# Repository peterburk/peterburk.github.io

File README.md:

# About Me

##Current Location
Auckland, New Zealand

##Email
peterburk at gmail dot com

##Qualifications
- MEng Electronic Systems Engineering, Lancaster University: First-class Honours
- International Baccalaureate

##Awards
- Lancaster Award (extra-curricular)
- IET Scholarship

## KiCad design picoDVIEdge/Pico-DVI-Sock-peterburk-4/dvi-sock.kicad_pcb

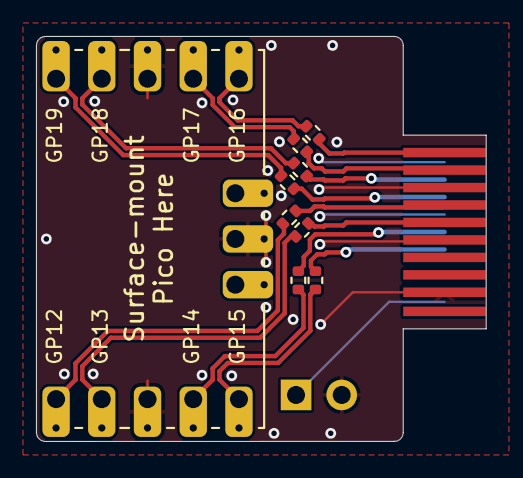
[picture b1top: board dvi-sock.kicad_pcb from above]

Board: 2 copper layers, 25.0 x 22.5 mm, 13 parts (0 on the bottom side), 18 nets.

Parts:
J1, J2: Conn_01x05; castellated_2.54mm_smd_x5
J3: Conn_01x03; castellated_2.54mm_smd_x3
J5: 2.54mm_2p_nofit; PinHeader_1x02_P2.54mm_Vertical_nosilk
R1, R2, R3, R4, R5, R6, R7, R8: 270; R_0402_1005Metric
U1: hdmiFemale

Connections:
+5V: J5.1, U1.18 +5V PWR
/CK+: R7.2, U1.10 TMDS CLK+
/CK-: R8.2, U1.12 TMDS CLK-
/D0+: R5.2, U1.7 TMDS Channel 0+
/D0-: R6.2, U1.9 TMDS Channel 0-
/D1+: R3.2, U1.4 TMDS Channel 1+
/D1-: R4.2, U1.6 TMDS Channel 1 -
/D2+: R1.2, U1.1 TMDS Channel 2+
/D2-: R2.2, U1.3 TMDS Channel 2-
/PICO_CK+: J1.4, R7.1
/PICO_CK-: J1.5, R8.1
/PICO_D0+: J1.1, R5.1
/PICO_D0-: J1.2, R6.1
/PICO_D1+: J2.4, R3.1
/PICO_D1-: J2.5, R4.1
/PICO_D2+: J2.1, R1.1
/PICO_D2-: J2.2, R2.1
GND: J1.3, J2.3, J3.2, J5.2, U1.2 TMDS Channel 2 GND, U1.5 TMDS Channel 1 GND, U1.8 TMDS Channel 0 GND, U1.11 TMDS CLK GND, U1.17 DDC/CEC GND

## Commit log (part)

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2014-05-09 php redirect
2014-05-09 html redirect
2014-05-09 Create gh-pages branch via GitHub
2014-05-11 YouLing
2014-05-11 Social
2014-05-11 Verse
2014-05-11 DigitalNative
2014-05-11 Social Redirect
2014-05-11 Social remov
2014-05-11 Social readd
2014-05-11 Folders
2014-05-11 Social fix
2014-05-11 Social remove
2014-06-26 Adding MOBAC profiles
2014-06-26 Removing MOBAC profiles
2015-10-08 Added images
2015-10-08 Moved blog to other repo
2015-10-08 Website front page text, photo
2015-10-08 Adding photo to readme
2015-10-12 Smaller headings in info.md
2015-10-12 Added noise background.jpg
2015-10-12 Photo id
2015-10-12 Index and blog
2015-10-12 Index
2015-10-12 Blog scripts
2015-10-12 Blog background image
2015-10-12 Blog title
2015-10-12 Ideas
2015-10-12 Hints
2015-10-12 Maps
2015-10-12 Programs
2015-10-12 Documents
2015-10-12 Contact
2015-10-12 Programs link
2015-10-12 Redirect
2015-10-12 Contact mailto
2016-01-13 iPod Nano Blog
2016-01-13 iPod Nano
2016-01-27 Verse to Github
2016-02-22 NZ Bus to Naz map
2016-03-07 Programs link from index
2016-10-26 Adding TurtleSheet
2016-10-28 TRA map finished
2016-10-28 TRA map blog page
2016-10-28 Railway button
2016-10-28 Fixed unfilled circles around Hsinchu
2016-10-28 Added Alishan Forest Railway
2016-10-28 Alishan Forest Railway ZH-TW
2017-01-16 Adding translate
2017-01-16 Translate from main page
2017-01-16 Translate numbers
2017-01-16 Translate with paragraph breaks
2017-01-17 Alternating lines
2017-03-22 TRA map now links to Himawari
2017-03-24 Added timetable
2017-03-24 Added timetable HTML
2017-04-27 added hsr
2017-04-27 ibus
2017-04-27 moving maps and ibus to repos
2017-04-28 kaohsiung 15 map
2017-04-28 removed kaohsiung map
2017-11-10 PlinyPedia
2017-11-10 Link to PlinyPedia
2017-11-10 Pliny Search to UTF-8
2017-11-10 Pliny files to UTF-8
2017-11-10 Added link to HN
2017-11-10 month names
2017-11-10 added mobile icon
2017-11-17 Chord Progressions
2018-04-22 sortlikes
2018-06-19 i2018n
2018-06-19 i2018 links
2018-06-19 removing titles
2018-07-17 adding pagefish
2018-07-17 added pagefish github benchmark
2018-07-17 added hash distribution graph
2019-12-23 TRA index page: Update Himawari Design links
2020-02-10 nanoLyrics
2020-02-10 nanoLyrics links
2020-02-10 nanoLyrics readme
2020-11-04 BinaRemote interview solution
2020-11-04 BinaRemote interview solution, fixing tabs
2020-11-04 BinaRemote interview solution, unknown button pressed
2020-11-06 nounIsLikeANoun
2021-04-23 Updating to github.io relative links instead of github.com hardlinks due to github policy change
2021-10-19 NanoLyrics KTV, NLT datasets
2021-10-25 Ed and the Awk
2022-01-06 ktv redirect
2022-01-14 20 years of wolfram
2024-02-26 PicoDVI Edge Connector
2025-03-18 rplan
2025-03-18 RPlan update
2025-05-24 YouTube redirects
2025-06-02 RPlan newline fix
2025-06-22 Update chordProgressions article due to feedback from Chris
